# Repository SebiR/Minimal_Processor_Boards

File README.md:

# Minimal Controller Boards

A collection of small microcontroller boards for different kinds of controllers with minimal external components, some LEDs and some switches

They have no real purpose. Maybe as an educational board to learn soldering and programming?

The ICSP/ISP/... connector is exposed, but you'll need the programmer accordingly.

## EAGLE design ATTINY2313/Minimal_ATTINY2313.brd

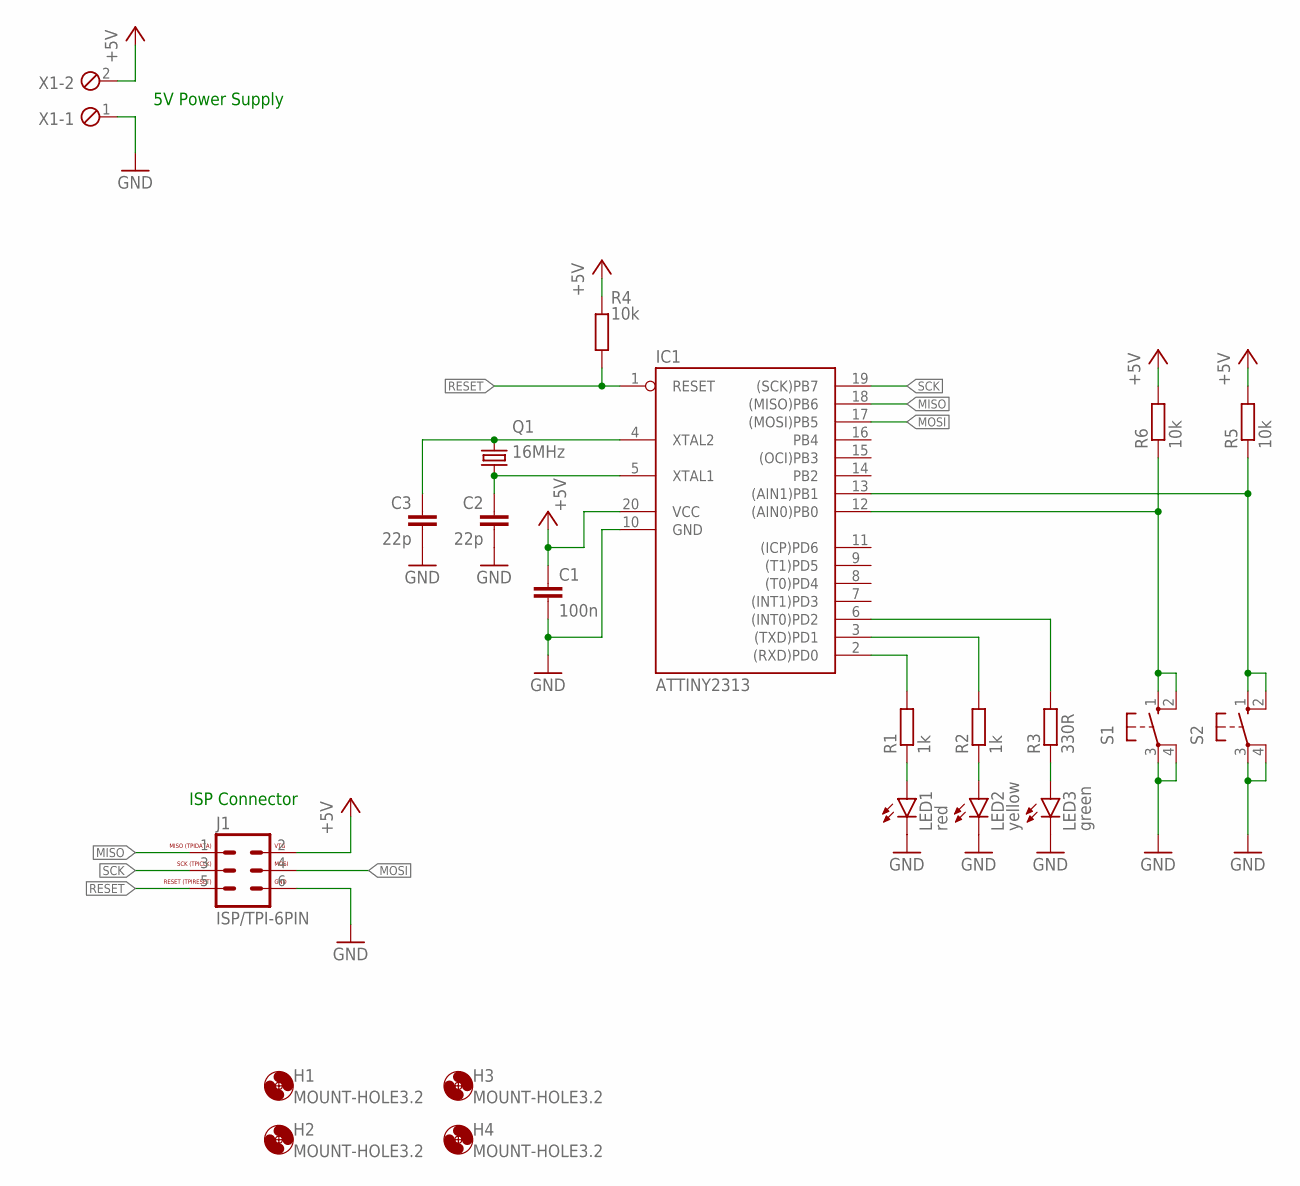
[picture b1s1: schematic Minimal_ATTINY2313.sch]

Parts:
C1: 100n; C050-024X044
C2, C3: 22p; C025-025X050
H1, H2, H3, H4: MOUNT-HOLE3.2; 3,2
IC1: ATTINY2313; DIL20
J1: ISP/TPI-6PIN; ML6
LED1: red; LED5MM
LED2: yellow; LED5MM
LED3: green; LED5MM
Q1: 16MHz; HC49U-V
R1, R2: 1k; 0207/5V
R3: 330R; 0207/5V
R4, R5, R6: 10k; 0207/5V
S1, S2: 10-XX; B3F-10XX
X1: MPT2; 2POL254

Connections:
+5V: C1.1, IC1.20 (VCC), J1.2, R4.1, R5.2, R6.2, X1.2
GND: C1.2, C2.2, C3.2, IC1.10 (GND), J1.6, LED1.K (C), LED2.K (C), LED3.K (C), S1.3, S1.4 (P1), S2.3, S2.4 (P1), X1.1
MISO: IC1.18 ((MISO)PB6), J1.1
MOSI: IC1.17 ((MOSI)PB5), J1.4
unnamed: C3.1, IC1.4 (XTAL2), Q1.2
unnamed: C2.1, IC1.5 (XTAL1), Q1.1
unnamed: IC1.2 ((RXD)PD0), R1.2
unnamed: IC1.3 ((TXD)PD1), R2.2
unnamed: IC1.6 ((INT0)PD2), R3.2
unnamed: LED1.A, R1.1
unnamed: LED2.A, R2.1
unnamed: LED3.A, R3.1
unnamed: IC1.12 ((AIN0)PB0), R6.1, S1.1 (S), S1.2 (S1)
unnamed: IC1.13 ((AIN1)PB1), R5.1, S2.1 (S), S2.2 (S1)
RESET: IC1.1 (RESET), J1.5, R4.2
SCK: IC1.19 ((SCK)PB7), J1.3

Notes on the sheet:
5V Power Supply
ISP Connector

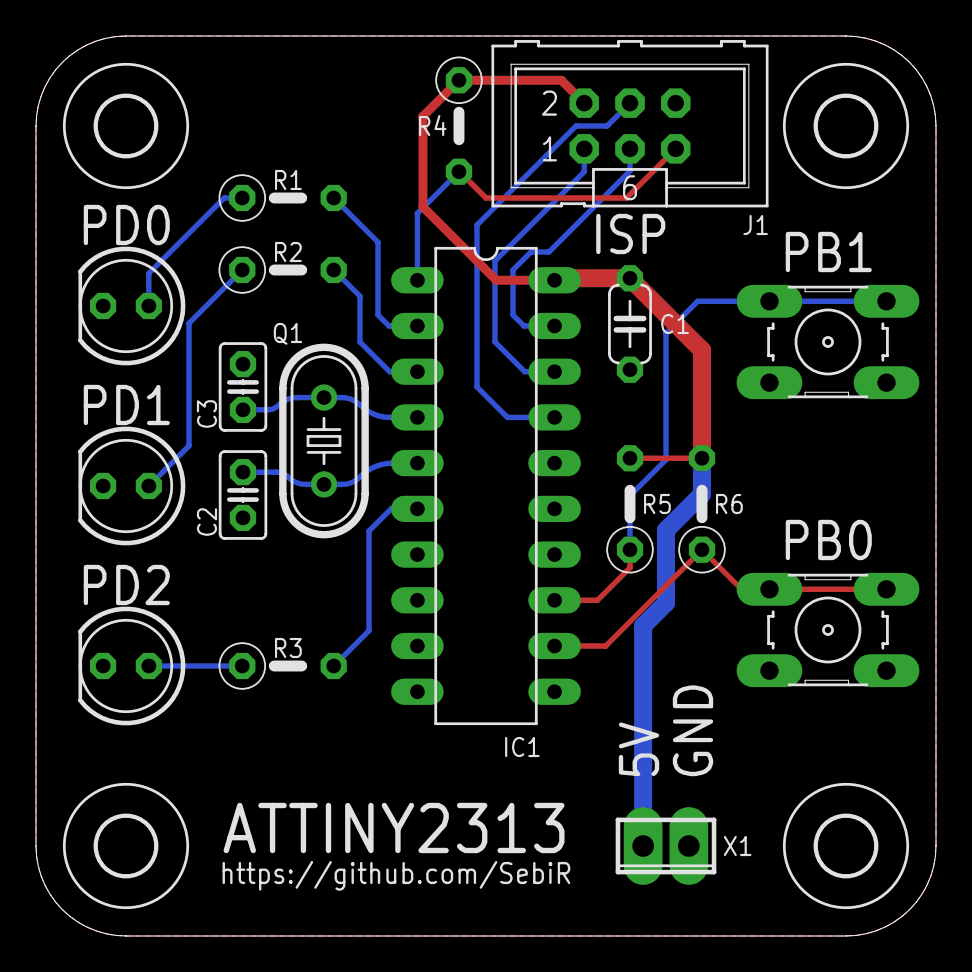
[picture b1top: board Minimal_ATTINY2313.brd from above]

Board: 2 copper layers, 50.0 x 50.0 mm, 22 parts (0 on the bottom side), 16 nets.

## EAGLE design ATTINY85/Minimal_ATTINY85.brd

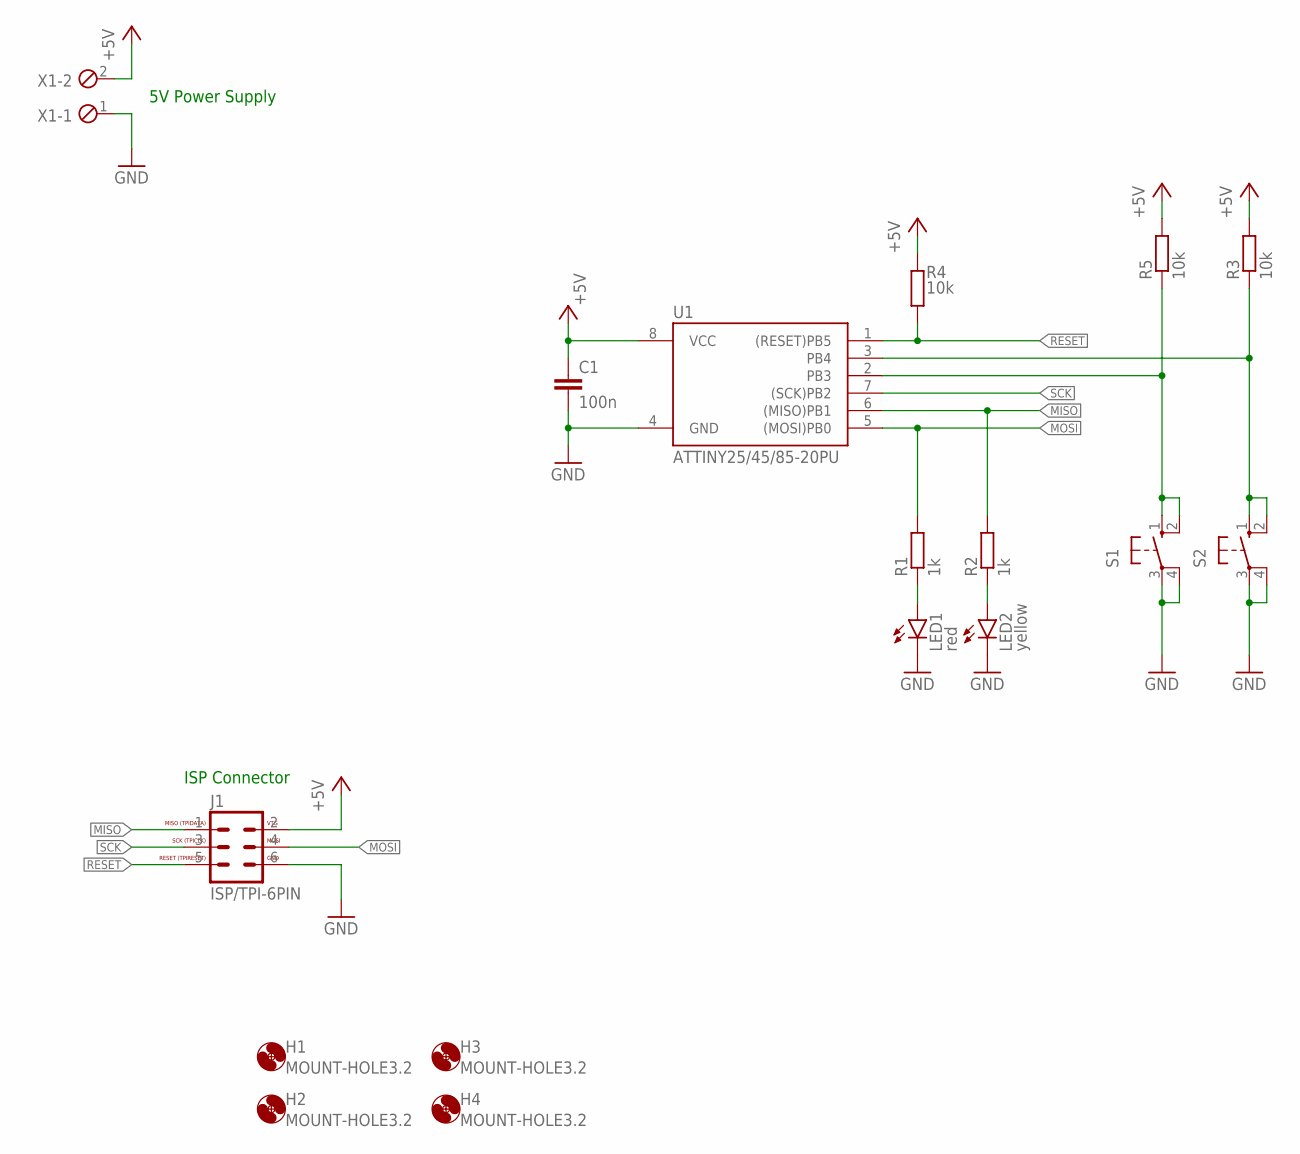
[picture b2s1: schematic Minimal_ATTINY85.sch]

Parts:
C1: 100n; C050-024X044
H1, H2, H3, H4: MOUNT-HOLE3.2; 3,2
J1: ISP/TPI-6PIN; ML6
LED1: red; LED5MM
LED2: yellow; LED5MM
R1, R2: 1k; 0207/5V
R3, R4, R5: 10k; 0207/5V
S1, S2: 10-XX; B3F-10XX
U1: ATTINY25/45/85-20PU; DIL08
X1: MPT2; 2POL254

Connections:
+5V: C1.1, J1.2, R3.2, R4.1, R5.2, U1.8 (VCC), X1.2
GND: C1.2, J1.6, LED1.K (C), LED2.K (C), S1.3, S1.4 (P1), S2.3, S2.4 (P1), U1.4 (GND), X1.1
MISO: J1.1, R2.2, U1.6 ((MISO)PB1)
MOSI: J1.4, R1.2, U1.5 ((MOSI)PB0)
unnamed: LED1.A, R1.1
unnamed: LED2.A, R2.1
unnamed: R5.1, S1.1 (S), S1.2 (S1), U1.2 (PB3)
unnamed: R3.1, S2.1 (S), S2.2 (S1), U1.3 (PB4)
RESET: J1.5, R4.2, U1.1 ((RESET)PB5)
SCK: J1.3, U1.7 ((SCK)PB2)

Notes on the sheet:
5V Power Supply
ISP Connector

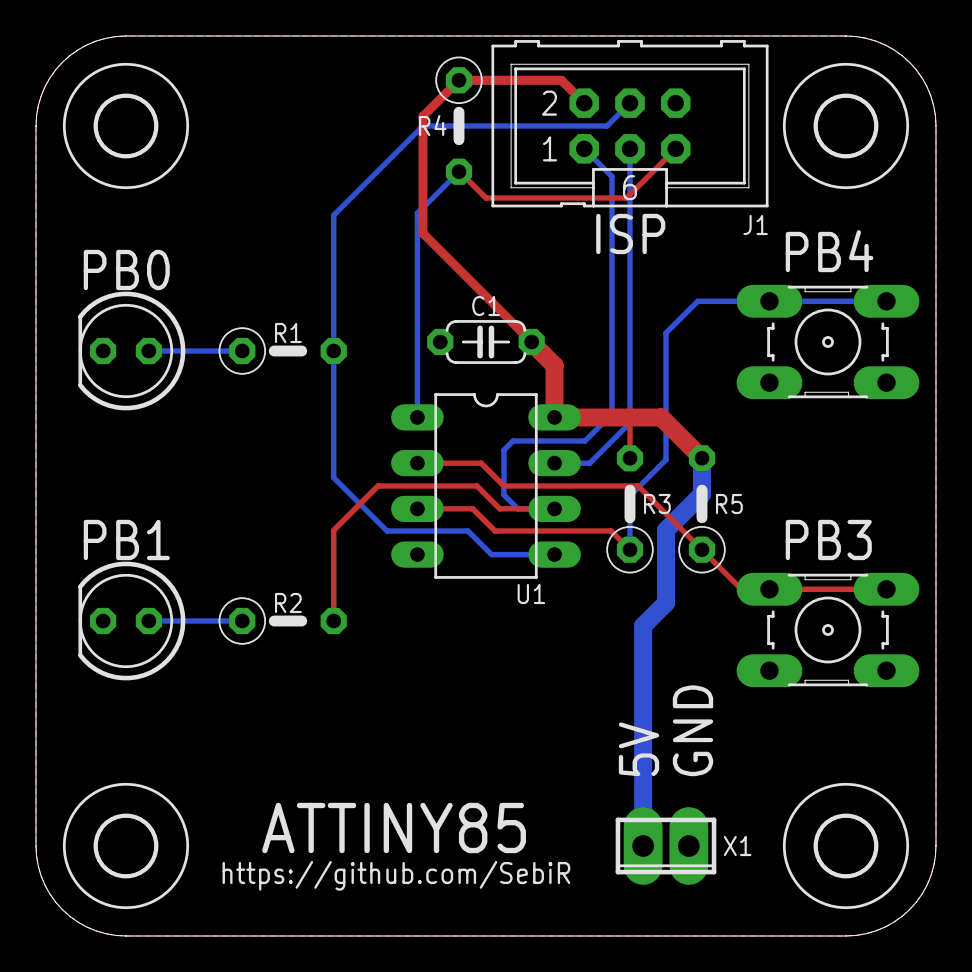
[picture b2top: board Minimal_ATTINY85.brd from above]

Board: 2 copper layers, 50.0 x 50.0 mm, 17 parts (0 on the bottom side), 10 nets.
